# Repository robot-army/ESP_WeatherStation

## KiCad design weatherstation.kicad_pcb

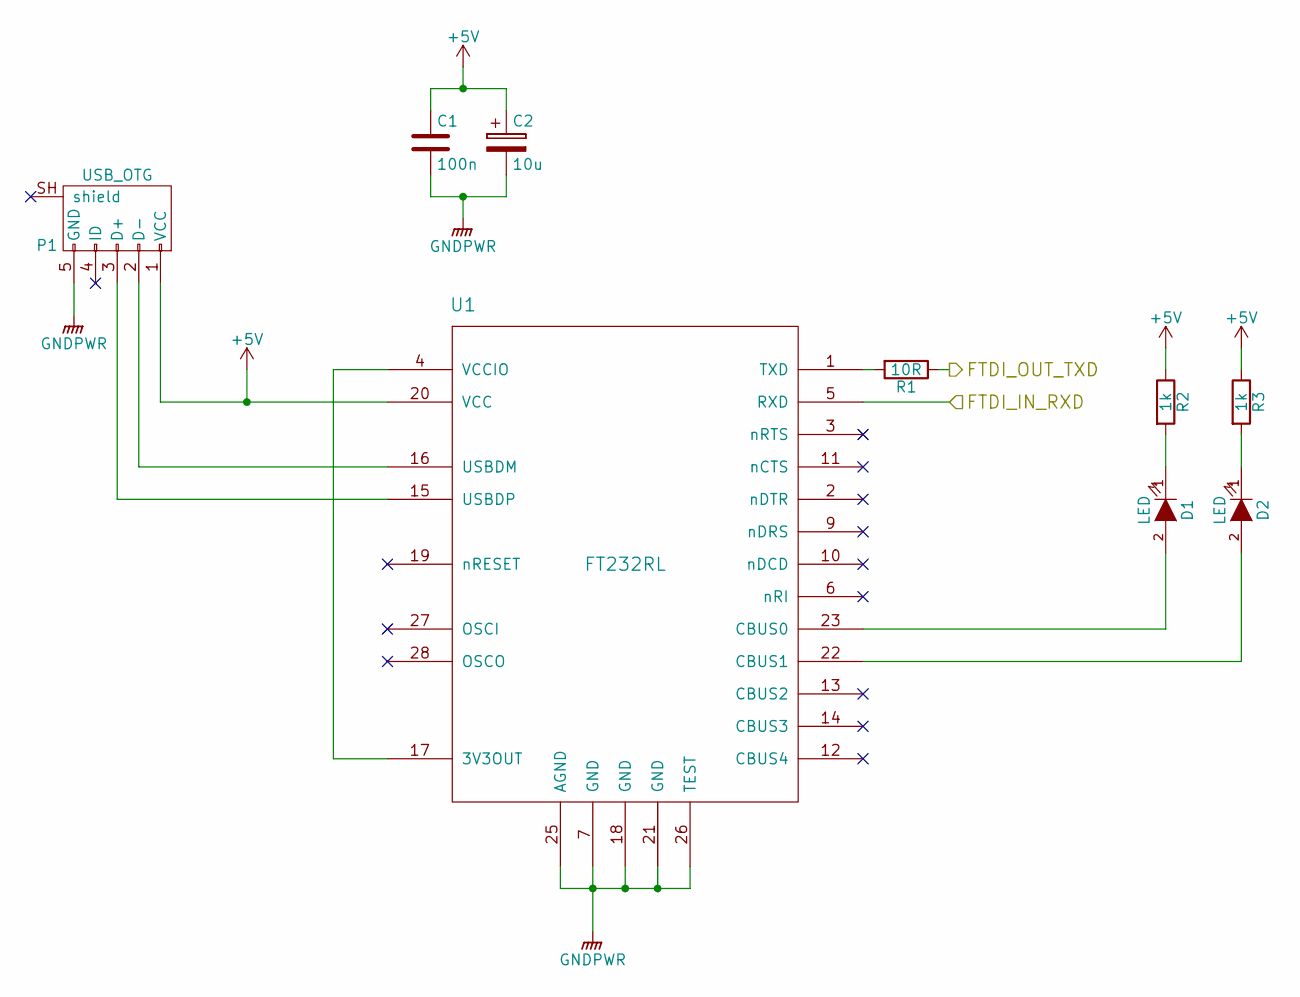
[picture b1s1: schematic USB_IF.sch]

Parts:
C1: 100n; R_0603_HandSoldering
C2: 10u; R_0805_HandSoldering
D1, D2: LED; R_0805_HandSoldering
P1: USB_OTG; USB_Micro-B
R1: 10R; R_0805_HandSoldering
R2, R3: 1k; R_0805_HandSoldering
U1: FT232RL; SSOP-28_5.3x10.2mm_Pitch0.65mm

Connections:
+5V: C1.1, C2.1, P1.1 (VCC), R2.1, R3.1, U1.20 (VCC); also elsewhere on the board
/ESP_module/ESP_IN_RXD: R1.1; also elsewhere on the board
/ESP_module/ESP_OUT_TXD: U1.5 (RXD); also elsewhere on the board
GNDPWR: C1.2, C2.2, P1.5 (GND), U1.7 (GND), U1.18 (GND), U1.21 (GND), U1.25 (AGND), U1.26 (TEST); also elsewhere on the board
unnamed: D1.1 (K), R2.2
unnamed: D1.2 (A), U1.23 (CBUS0)
unnamed: D2.1 (K), R3.2
unnamed: D2.2 (A), U1.22 (CBUS1)
unnamed: P1.2 (D-), U1.16 (USBDM)
unnamed: P1.3 (D+), U1.15 (USBDP)
unnamed: R1.2, U1.1 (TXD)
unnamed: U1.4 (VCCIO), U1.17 (3V3OUT)

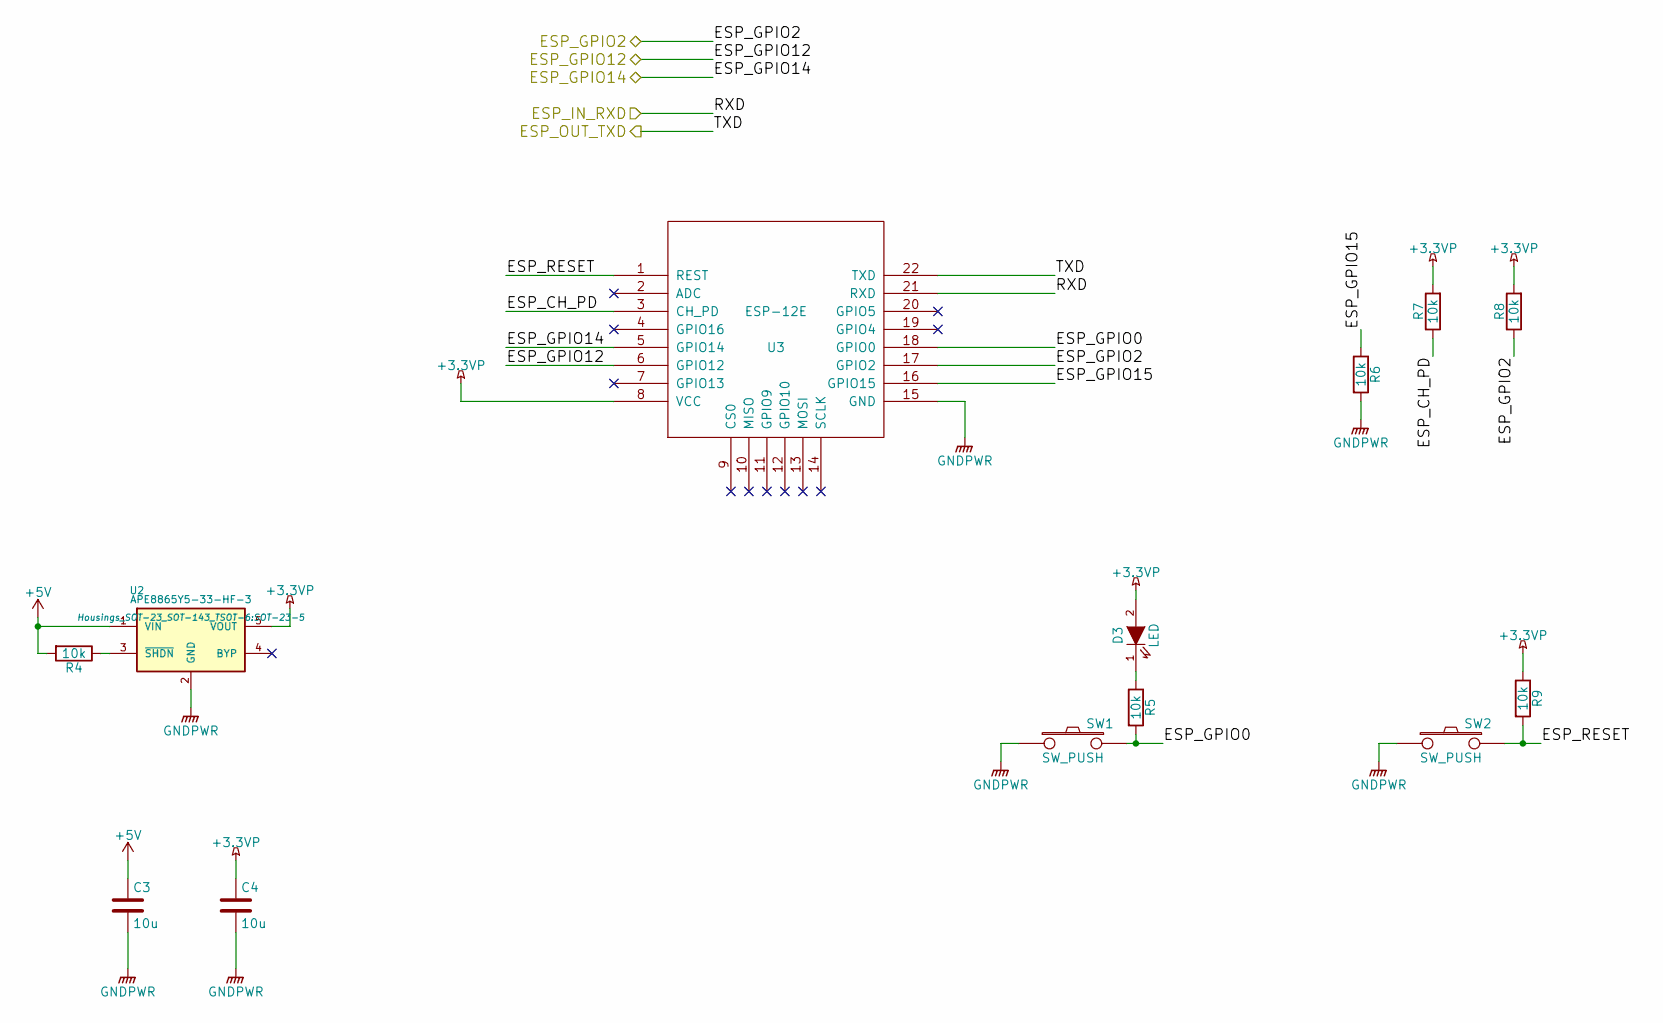
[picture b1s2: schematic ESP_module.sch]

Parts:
C3, C4: 10u; R_0603_HandSoldering
D3: LED; R_0805_HandSoldering
R4, R5, R6, R7, R8, R9: 10k; R_0805_HandSoldering
SW1, SW2: SW_PUSH; SW_SPST_EVQP2
U2: APE8865Y5-33-HF-3; SOT-23-5
U3: ESP-12E

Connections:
+3.3VP: C4.1, D3.2 (A), R7.2, R8.2, R9.1, U2.5 (VOUT), U3.8 (VCC)
+5V: C3.1, R4.2, U2.1 (VIN); also elsewhere on the board
/ESP_module/ESP_CH_PD: R7.1, U3.3 (CH_PD)
/ESP_module/ESP_GPIO0: R5.2, SW1.2, U3.18 (GPIO0)
/ESP_module/ESP_GPIO15: R6.1, U3.16 (GPIO15)
/ESP_module/ESP_IN_RXD: U3.21 (RXD); also elsewhere on the board
/ESP_module/ESP_OUT_TXD: U3.22 (TXD); also elsewhere on the board
/ESP_module/ESP_RESET: R9.2, SW2.2, U3.1 (REST)
/display/DISP_RST: R8.1, U3.17 (GPIO2); also elsewhere on the board
/display/DISP_SCL: U3.6 (GPIO12); also elsewhere on the board
/display/DISP_SDA: U3.5 (GPIO14); also elsewhere on the board
GNDPWR: C3.2, C4.2, R6.2, SW1.1, SW2.1, U2.2 (GND), U3.15 (GND); also elsewhere on the board
unnamed: D3.1 (K), R5.1
unnamed: R4.1, U2.3 (~SHDN~)

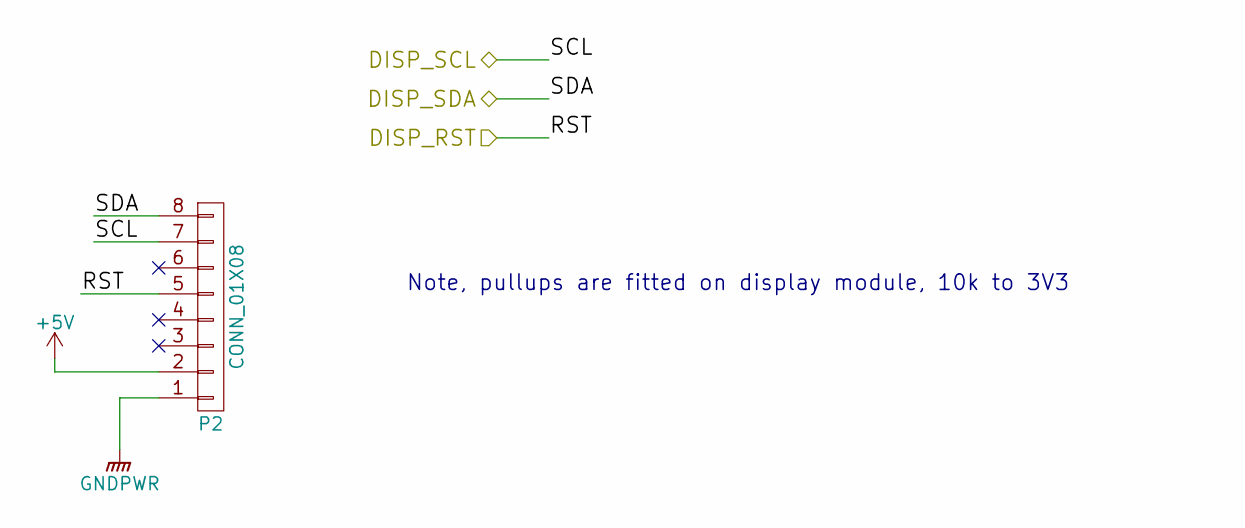
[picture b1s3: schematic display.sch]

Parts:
P2: CONN_01X08; Pin_Header_Straight_1x08

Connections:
+5V: P2.2; also elsewhere on the board
/display/DISP_RST: P2.5; also elsewhere on the board
/display/DISP_SCL: P2.7; also elsewhere on the board
/display/DISP_SDA: P2.8; also elsewhere on the board
GNDPWR: P2.1; also elsewhere on the board

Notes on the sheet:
Note, pullups are fitted on display module, 10k to 3V3

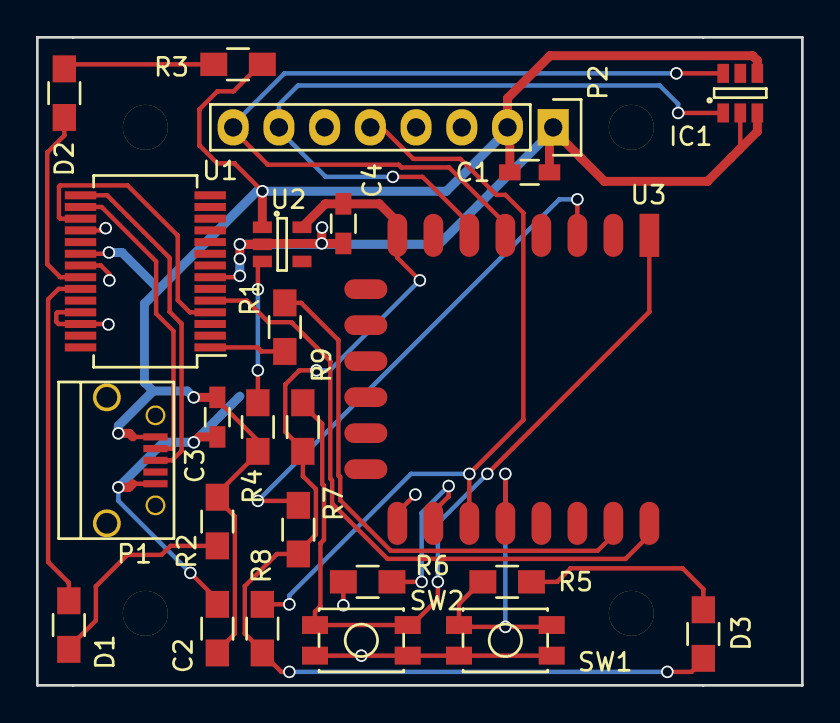
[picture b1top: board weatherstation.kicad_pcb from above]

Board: 2 copper layers, 42.5 x 36.0 mm, 24 parts (0 on the bottom side), 22 nets.

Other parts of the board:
IC1: TMP100; SOT-23-6

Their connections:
+5V: IC1.4; also elsewhere on the board
/display/DISP_SCL: IC1.1; also elsewhere on the board
/display/DISP_SDA: IC1.6; also elsewhere on the board
GNDPWR: IC1.2, IC1.3; also elsewhere on the board

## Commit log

2015-11-09 Added root and hierarchical schematics, cache and mostly blank board
2015-11-09 Added PDF
2015-11-09 Fixed PDF orientation
2015-11-10 Started adding component values and tidying up
2015-11-10 added component values and most packages. Still missing micro usb
2015-11-10 Added a USB socket with GND set as a power output to pass DRC, and gave a first stab at a placement. Man that's tight! Components both side required??
2015-11-12 Added placement screenshot to show how tight this thing is going to be
2015-11-16 Dodgy layout added, etc
2015-11-16 Added some RS part numbers for switches and usb
2015-11-16 Added some RS part numbers
2015-11-16 Added first layout with all tracks routed. Bit ugly, needs logo and sensor added
2015-11-16 Fixed layout up a bit
2015-11-16 Added logo, sensor, manufacturing data'
2015-11-16 Fixed track too close to FTDI chip
2015-11-16 Added BOM with RS numbers
2015-11-16 Added new PDF
2015-11-16 added svg of board
2015-11-17 Added manufacturing files, fixed rear text, moved tracks away from mounting holes and added vias to ground plane
2015-11-22 Arduino Code Init
2015-11-22 costs on mom
2016-01-12 Fixed libarary paths
2016-01-12 Removed submodules because git FAWERAAWEIAFJOIJWEHUOARAAAAAAAAAH
